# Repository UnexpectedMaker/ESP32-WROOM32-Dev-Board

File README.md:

# ESP32-WROOM32-Dev-Board
I decided a while back that I wanted to design, build and open source a WROOM32 ESP32 development board that was designed to plug a 2.1mm 5V power supply directly into it to drive high loads like hundreds of SK6812B's or 64x32 RGB Matrix Panels.

My revision 2 board works great, but uses a fairly expensive FT231XS FTDI USB Serial chip, so I thought I'd try to redesign it to use a cheap CH340C USB chip that has a built in oscillator to reduce parts.

My aim was to drive the CH340C from 3.3V and not 5V, and the data sheets suggests this is possible, but from my experience, it’s a terrible implementation.

So I have 2x CH340C folders…
Rev4 - CH340C driven from 3.3V
Rev5 - CH340C driven from 5V

Feel free to give the 3.3V version a whirl and if you can get ti working, please let me know how!

Anyway, this was just an experiment and it’s been a fun and frustrating journey, but I learnt a lot doing this and I’ve learnt stacks more since starting this project, so it’s time to let the files out into the wild so others can have a play with them. 

Enjoy!

# Support Unexpected Maker

I love designing, making and releasing my projects as open source. I do it because I believe it’s important to share knowledge and give back to the community, like many have done before me. It helps us all learn and grow.

That said, a lot of time, effort and finances have gone into designing and releasing these files, so please consider supporting me by buying some of my products:

https://unexpectedmaker.com/shop

https://www.tindie.com/stores/seonr/

Or by becoming a Patron:

https://www.patreon.com/unexpectedmaker

# Join my discord server
https://discord.com/invite/xAHpApP

# Unexpected Maker
https://unexpectedmaker.com

http://youtube.com/unexpectedmaker

http://twitter.com/unexpectedmaker

https://www.facebook.com/unexpectedmaker/

https://www.instagram.com/unexpectedmaker/

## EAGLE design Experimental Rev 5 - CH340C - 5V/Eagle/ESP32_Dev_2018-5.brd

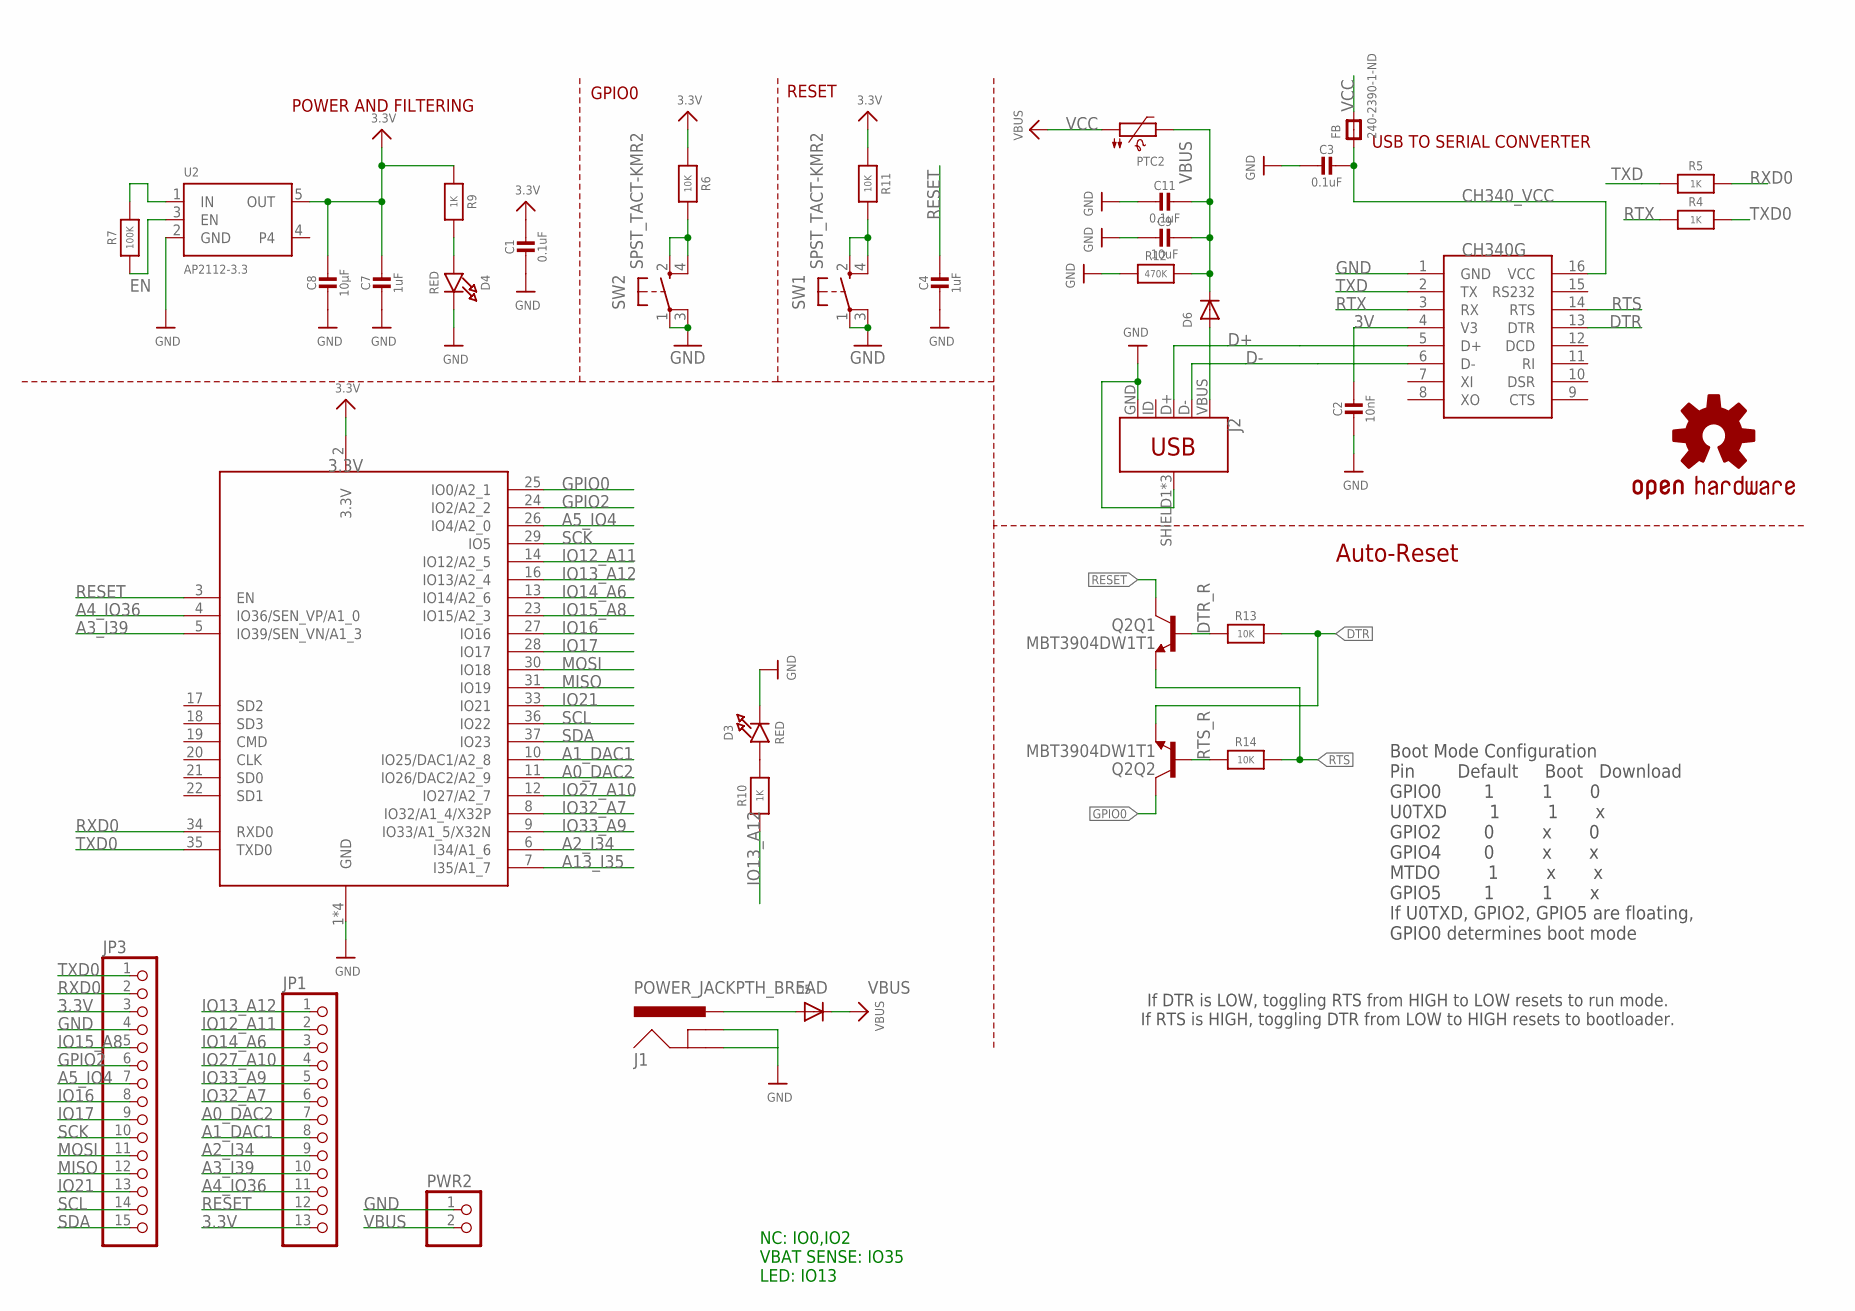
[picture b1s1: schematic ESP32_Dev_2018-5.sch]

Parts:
C1, C3, C11: 0.1uF; 0805-NO
C2: 10nF; 0805-NO
C4, C7: 1uF; 0805-NO
C8: 10µF; 0805-NO
C9: 10uF; 0805-NO
CH340C: CH340C; SOIC16
D3, D4: RED; CHIPLED_0805_NOOUTLINE
D5, D6: DIODESOD-123; SOD-123
FB: 240-2390-1-ND; _0805
J1: POWER_JACKPTH_BREAD; POWER_JACK_PTH_BREAD
J2: USB_MICRO-BREDUCED_PASTE; USB-B-MICRO-SMD_RED_PASTE
JP1: HEADER-1X13; 1X13_ROUND_70
JP3: HEADER-1X15; 1X15_ROUND_70
LOGO1: OSHW-LOGOM; OSHW-LOGO-M
PTC2: PTC1206; 1206
PWR2: HEADER-1X2ROUND; 1X02_ROUND
Q2: MBT3904DW1T1; SC70-6
R4, R5, R9, R10: 1K; 0805-NO
R6, R11, R13, R14: 10K; 0805-NO
R7: 100K; 0805-NO
R12: 470K; 0805-NO
SW1, SW2: SPST_TACT-KMR2; KMR2
U2: AP2112-3.3; SOT23-5
X2: ESP32_WROOM32; WROOM32

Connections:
3.3V: C1.1, C7.1, C8.1, JP1.13, JP3.3, R6.1, R9.1, R11.1, U2.5 (OUT), X2.2 (3.3V)
3V: C2.1, CH340C.4 (V3)
A0_DAC2: JP1.7, X2.11 (IO26/DAC2/A2_9)
A1_DAC1: JP1.8, X2.10 (IO25/DAC1/A2_8)
A2_I34: JP1.9, X2.6 (I34/A1_6)
A3_I39: JP1.10, X2.5 (IO39/SEN_VN/A1_3)
A4_IO36: JP1.11, X2.4 (IO36/SEN_VP/A1_0)
A5_IO4: JP3.7, X2.26 (IO4/A2_0)
A13_I35: X2.7 (I35/A1_7)
CH340_VCC: C3.1, CH340C.16 (VCC), FB.1
D+: CH340C.5 (D+), J2.D+
D-: CH340C.6 (D-), J2.D-
DTR: CH340C.13 (DTR), Q2.1 (E), R13.2
DTR_R: Q2.5 (B), R13.1
EN: R7.1, U2.3 (EN)
GND: C1.2, C2.2, C3.2, C4.2, C7.2, C8.2, C9.2, C11.2, CH340C.1 (GND), D3.C, D4.C, J1.GND, J1.GNDBREAK, J2.GND, J2.SHIELD1 (SHIELD), J2.SHIELD2 (SHIELD), J2.SHIELD3 (SHIELD), JP3.4, PWR2.1, R12.1, SW1.1, SW1.3 (P1), SW2.1, SW2.3 (P1), U2.2 (GND), X2.1 (GND), X2.15 (GND), X2.38 (GND), X2.P$1 (GND)
GPIO0: Q2.6 (C), R6.2, SW2.2 (S), SW2.4 (S1), X2.25 (IO0/A2_1)
GPIO2: JP3.6, X2.24 (IO2/A2_2)
IO12_A11: JP1.2, X2.14 (IO12/A2_5)
IO13_A12: JP1.1, R10.1, X2.16 (IO13/A2_4)
IO14_A6: JP1.3, X2.13 (IO14/A2_6)
IO15_A8: JP3.5, X2.23 (IO15/A2_3)
IO16: JP3.8, X2.27 (IO16)
IO17: JP3.9, X2.28 (IO17)
IO21: JP3.13, X2.33 (IO21)
IO27_A10: JP1.4, X2.12 (IO27/A2_7)
IO32_A7: JP1.6, X2.8 (IO32/A1_4/X32P)
IO33_A9: JP1.5, X2.9 (IO33/A1_5/X32N)
MISO: JP3.12, X2.31 (IO19)
MOSI: JP3.11, X2.30 (IO18)
unnamed: D6.A, J2.VBUS
unnamed: D3.A, R10.2
unnamed: D4.A, R9.2
RESET: C4.1, JP1.12, Q2.3 (C), R11.2, SW1.2 (S), SW1.4 (S1), X2.3 (EN)
RTS: CH340C.14 (RTS), Q2.4 (E), R14.2
RTS_R: Q2.2 (B), R14.1
RTX: CH340C.3 (RX), R4.1
RXD0: JP3.2, R5.2, X2.34 (RXD0)
SCK: JP3.10, X2.29 (IO5)
SCL: JP3.14, X2.36 (IO22)
SDA: JP3.15, X2.37 (IO23)
TXD: CH340C.2 (TX), R5.1
TXD0: JP3.1, R4.2, X2.35 (TXD0)
VBUS: C9.1, C11.1, D5.C, D6.C, PTC2.2, PWR2.2, R12.2
VBUS1: D5.A, J1.PWR
VCC: FB.2, PTC2.1, R7.2, U2.1 (IN)

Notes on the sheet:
POWER AND FILTERING
RESET
USB TO SERIAL CONVERTER
NC: IO0,IO2 VBAT SENSE: IO35 LED: IO13
Boot Mode Configuration Pin Default Boot Download GPIO0 1 1 0 U0TXD 1 1 x GPIO2 0 x 0 GPIO4 0 x x MTDO 1 x x GPIO5 1 1 x If U0TXD, GPIO2, GPIO5 are floating, GPIO0 determines boot mode
Auto-Reset
If DTR is LOW, toggling RTS from HIGH to LOW resets to run mode. If RTS is HIGH, toggling DTR from LOW to HIGH resets to bootloader.
GPIO0

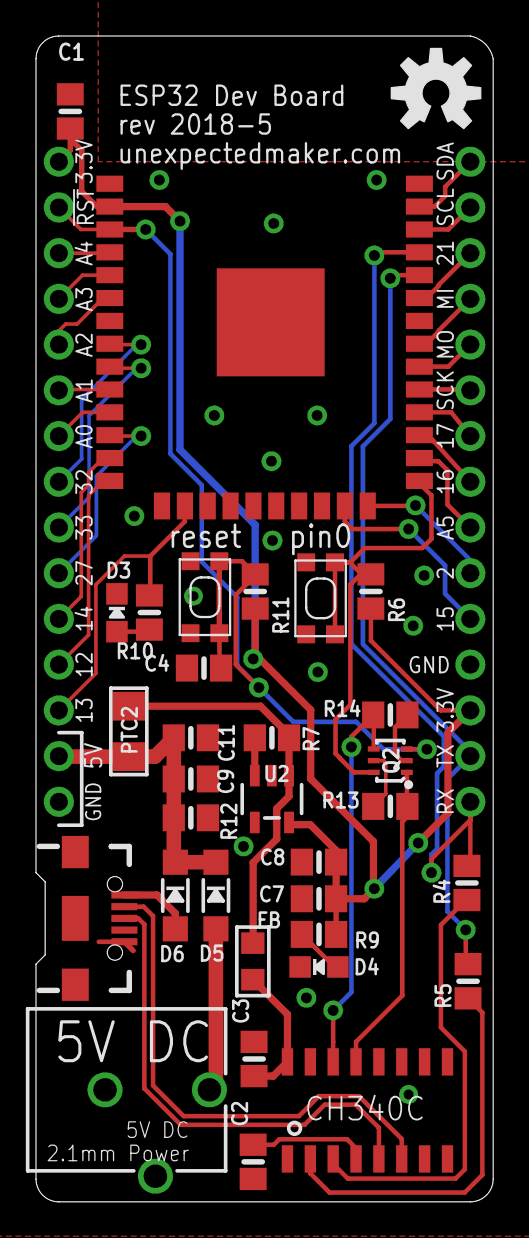
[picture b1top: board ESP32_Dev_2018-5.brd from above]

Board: 2 copper layers, 25.4 x 64.8 mm, 37 parts (1 on the bottom side), 45 nets.

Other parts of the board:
LOGO2: OSHW-LOGOM; OSHW-LOGO-M

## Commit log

2018-10-05 And the files, woops!

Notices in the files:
parts and their libraries:
microbuilder: This work is placed in the public domain, and may be freely used for commercial and non-commercial work with the following conditions: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
SparkFun-Connectors: Licensing: Creative Commons ShareAlike 4.0 International - https://creativecommons.org/licenses/by-sa/4.0
